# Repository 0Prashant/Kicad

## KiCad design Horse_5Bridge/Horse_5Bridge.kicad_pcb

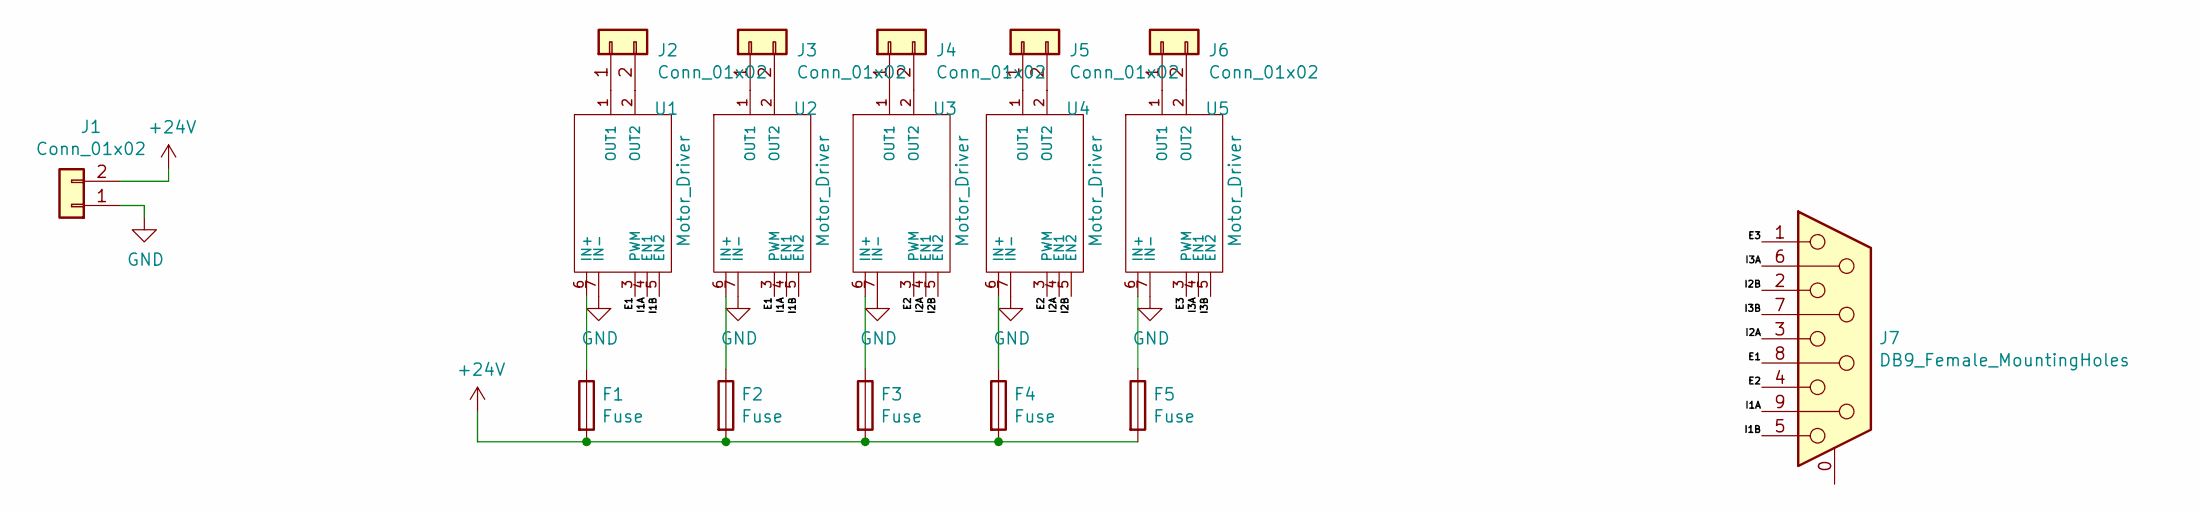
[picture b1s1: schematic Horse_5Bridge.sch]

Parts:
F1, F2, F3, F4, F5: Fuse; Fuse_Holder
J1, J2, J3, J4, J5, J6: Conn_01x02; Solar_Connector
J7: DB9_Female_MountingHoles; Connector_DB_9
U1, U2, U3, U4, U5: Motor_Driver; H_Bridge

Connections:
+24V: F1.2, F2.2, F3.2, F4.2, F5.2, J1.2
/E1: J7.8, U1.3 (PWM), U2.3 (PWM)
/E2: J7.4, U3.3 (PWM), U4.3 (PWM)
/E3: J7.1, U5.3 (PWM)
/I1A: J7.9, U1.4 (EN1), U2.4 (EN1)
/I1B: J7.5, U1.5 (EN2), U2.5 (EN2)
/I2A: J7.3, U3.4 (EN1), U4.4 (EN1)
/I2B: J7.2, U3.5 (EN2), U4.5 (EN2)
/I3A: J7.6, U5.4 (EN1)
/I3B: J7.7, U5.5 (EN2)
GND: J1.1, U1.7 (IN-), U2.7 (IN-), U3.7 (IN-), U4.7 (IN-), U5.7 (IN-)
unnamed: F1.1, U1.6 (IN+)
unnamed: F2.1, U2.6 (IN+)
unnamed: F3.1, U3.6 (IN+)
unnamed: F4.1, U4.6 (IN+)
unnamed: F5.1, U5.6 (IN+)
unnamed: J2.1, U1.1 (OUT1)
unnamed: J2.2, U1.2 (OUT2)
unnamed: J3.1, U2.1 (OUT1)
unnamed: J3.2, U2.2 (OUT2)
unnamed: J4.1, U3.1 (OUT1)
unnamed: J4.2, U3.2 (OUT2)
unnamed: J5.1, U4.1 (OUT1)
unnamed: J5.2, U4.2 (OUT2)
unnamed: J6.1, U5.1 (OUT1)
unnamed: J6.2, U5.2 (OUT2)

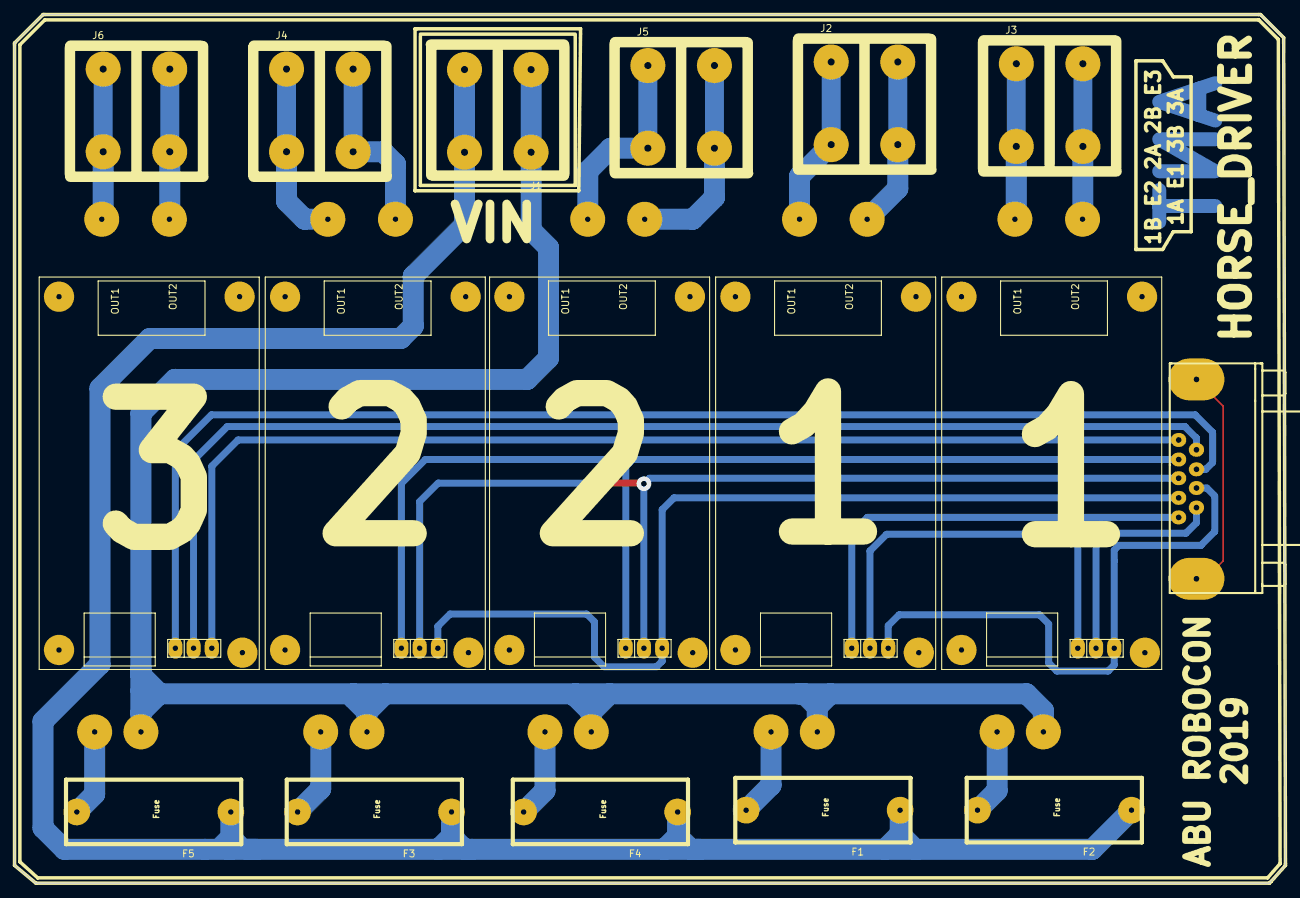
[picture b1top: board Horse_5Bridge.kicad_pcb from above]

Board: 2 copper layers, 181.4 x 124.0 mm, 17 parts (0 on the bottom side), 26 nets.

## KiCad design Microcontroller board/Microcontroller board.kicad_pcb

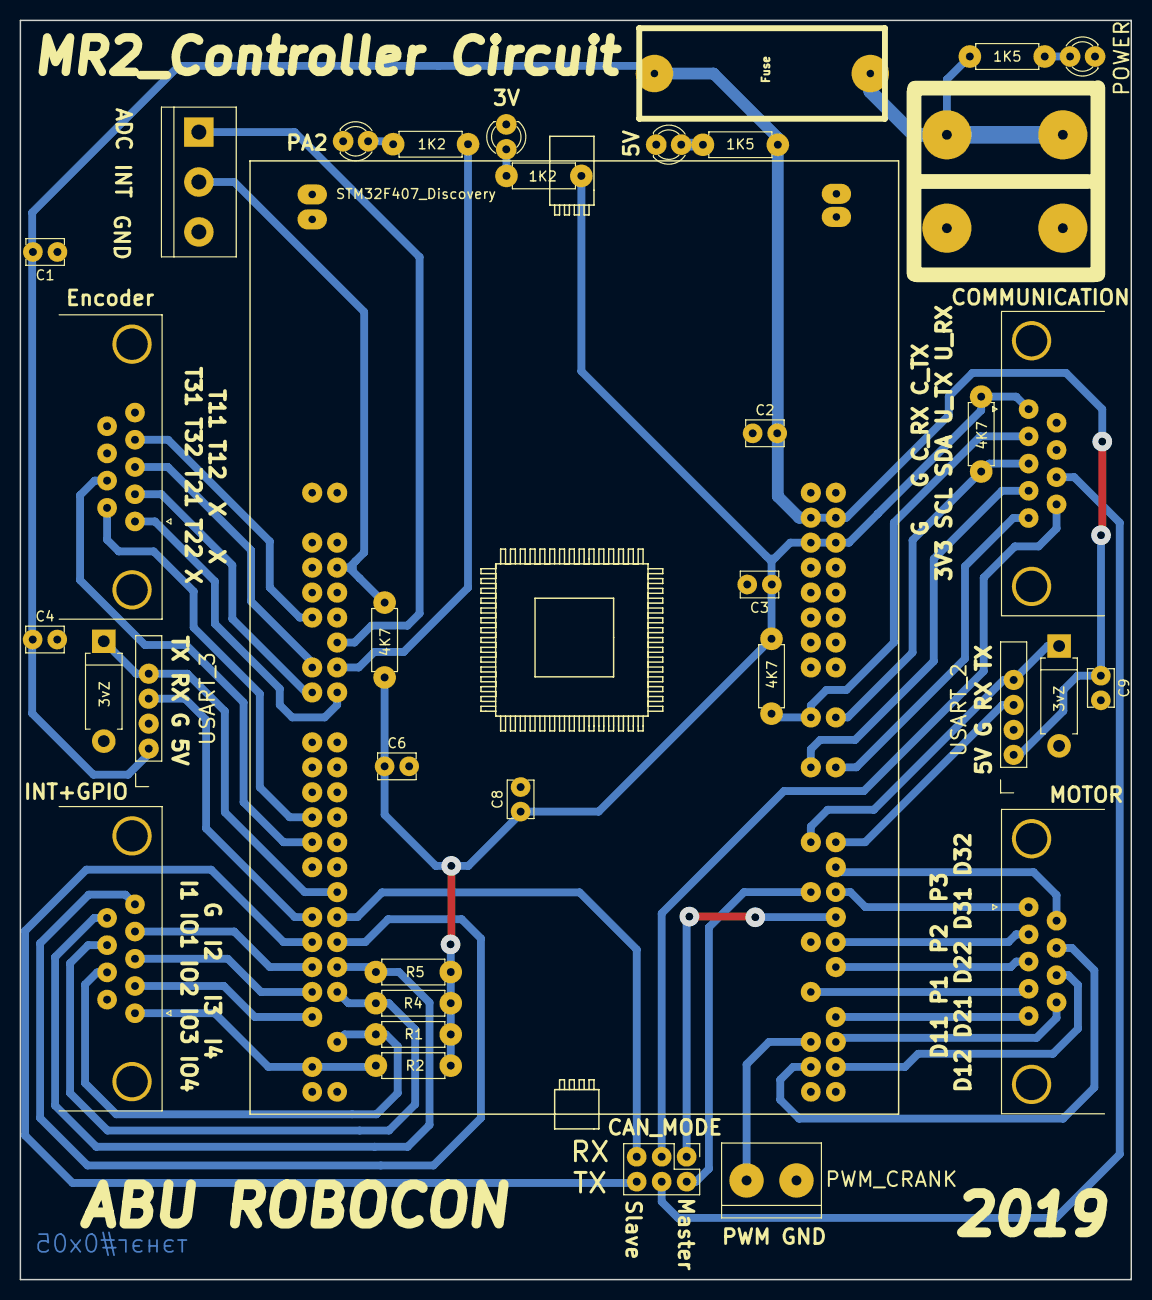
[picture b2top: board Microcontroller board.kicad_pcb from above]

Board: 2 copper layers, 113.0 x 128.1 mm, 36 parts (0 on the bottom side), 49 nets.

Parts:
3vZ, 3vZ#2: D_Zener; Diode_Small
4K7, 4K7#2: R; Resistor_small
C1, C2, C3, C4, C6, C8, C9: C; Capacitor_Disc_Small
D3, D4, D5, D6: LED; LED_D3.0mm
F1: Fuse; Fuse_Holder
J2: COMMUNICATION; DSUB-9_Female_Horizontal_P2.77x2.84mm_EdgePinOffset4.94mm_H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
J3: Encoder; DSUB-9_Female_Horizontal_P2.77x2.84mm_EdgePinOffset4.94mm_H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
J4: MOTOR; DSUB-9_Female_Horizontal_P2.77x2.84mm_EdgePinOffset4.94mm_H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
J5: USART_2; PinSocket_1x06_P2.54mm_Vertical
J6: INT+GPIO; DSUB-9_Female_Horizontal_P2.77x2.84mm_EdgePinOffset4.94mm_H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
J7: USART_3; PinSocket_1x06_P2.54mm_Vertical
J8: PWM_CRANK; Connector_Bornier_2
J9: INTERRUPT; TerminalBlock_bornier-3_P5.08mm
J11: POWER; Solar_Connector
R1, R2, R4, R5: R; Resistor_small
R7: 4K7; Resistor_small
R8, R9: 1K5; Resistor_small
R10, R11: 1K2; Resistor_small
U1: STM32F407_Discovery
`J10: CAN_MODE; PinHeader_2x03_P2.54mm_Vertical

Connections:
/3V3: 4K7.1, 4K7#2.2, C3.1, C6.1, C8.1, J2.1, R1.1, R2.1, R4.2, R5.2, R7.1, R11.2, U1.55, U1.56
/5V: C1.2, C2.2, C4.1, C9.1, F1.1, J5.2, J7.2, R9.2, U1.53, U1.54
/CAN_RX: J2.9, `J10.2
/CAN_TX: J2.8, `J10.5
/GND: 3vZ.2, 3vZ#2.2, C1.1, C2.1, C3.2, C4.2, C6.2, C8.2, C9.2, D3.1, D4.1, D5.1, D6.1, J2.0, J2.6, J2.7, J3.0, J4.0, J5.3, J6.0, J6.6, J7.3, J8.2, J9.3, J11.1, U1.1, U1.2, U1.5, U1.23, U1.49, U1.50, U1.51, U1.52, U1.99, U1.100
/PA1: J3.4, U1.11
/PA2: J9.1, U1.14
/PA4: R10.2, U1.16
/PA5: J3.3, U1.15
/PA6: J3.1, U1.18
/PA7: J3.2, U1.17
/PA9: J4.5, U1.94
/PA10: J4.4, U1.91
/PA15: J4.3, U1.90
/PB6: J2.4, U1.73
/PB7: J2.5, U1.74
/PB8: 4K7#2.1, J2.2, U1.69
/PB9: 4K7.2, J2.3, U1.70
/PB10: 3vZ#2.1, J7.5, U1.34
/PB11: J7.4, U1.35
/PB12: U1.36, `J10.3
/PB13: U1.37, `J10.6
/PB14: J6.5, U1.38
/PB15: J6.4, U1.39
/PC0: J9.2, R7.2, U1.8
/PC6: J4.7, U1.97
/PC7: J4.8, U1.98
/PC8: J8.1, U1.95
/PC9: J4.9, U1.96
/PC11: J4.2, U1.88
/PD0: U1.86, `J10.1
/PD1: U1.83, `J10.4
/PD2: J4.1, U1.84
/PD4: J4.6, U1.82
/PD5: 3vZ.1, J5.5, U1.79
/PD6: J5.4, U1.80
/PD8: J6.9, R5.1, U1.40
/PD9: J6.3, U1.41
/PD10: J6.8, R4.1, U1.42
/PD11: J6.2, U1.43
/PD14: J6.7, R1.2, U1.46
/PD15: J6.1, R2.2, U1.47
/PE9: J3.6, U1.27
/PE11: J3.7, U1.29
/Vin: F1.2, J11.2, R8.2
unnamed: D3.2, R8.1
unnamed: D4.2, R9.1
unnamed: D5.2, R10.1
unnamed: D6.2, R11.1

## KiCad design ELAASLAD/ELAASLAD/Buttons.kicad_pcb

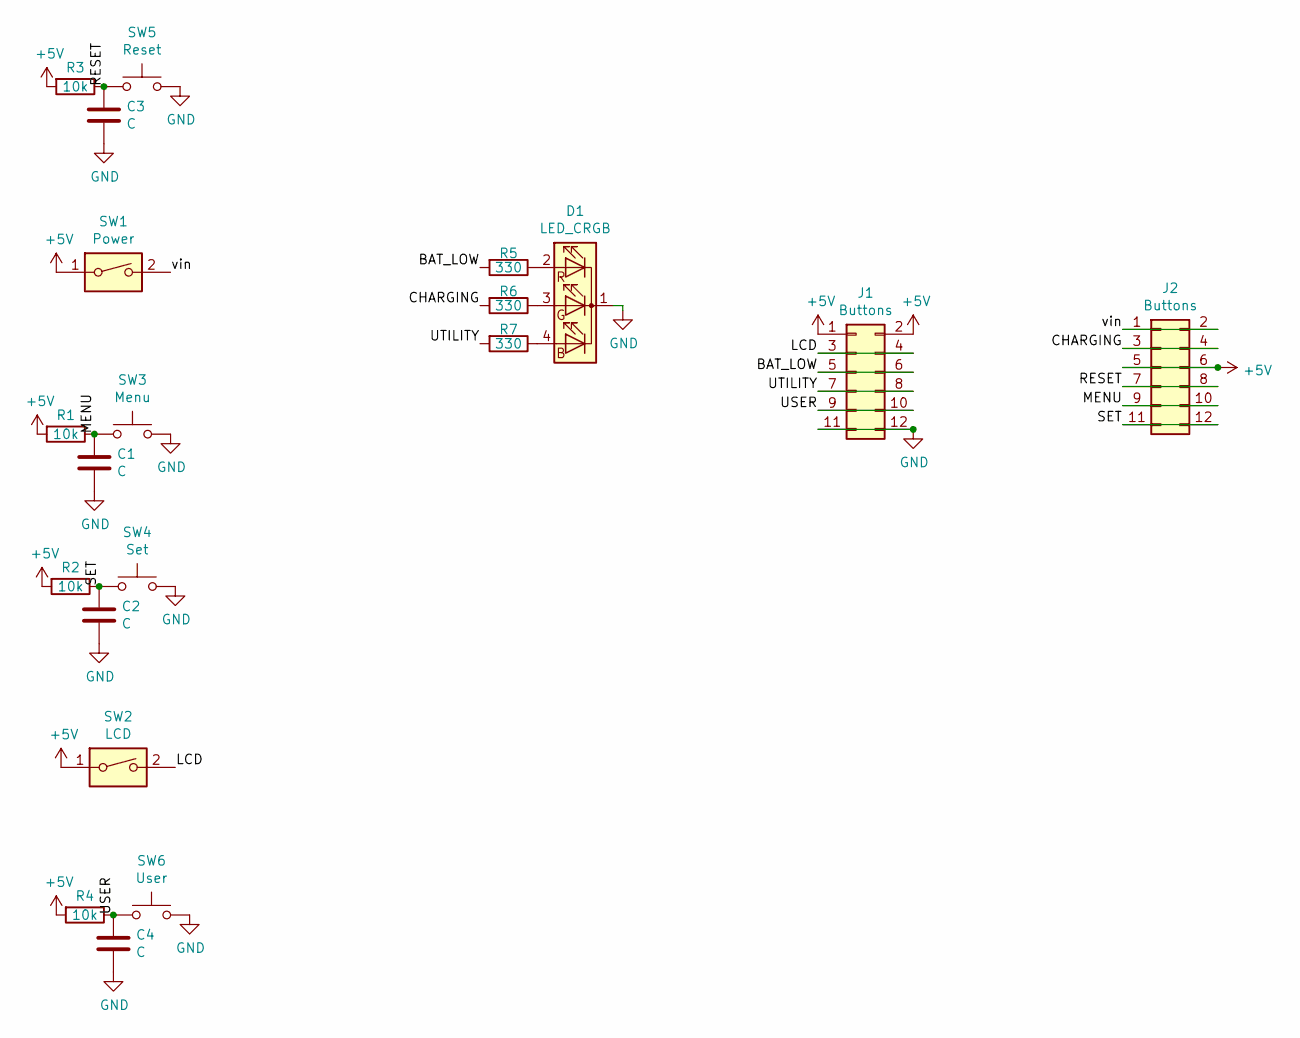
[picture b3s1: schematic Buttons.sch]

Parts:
C1, C2, C3, C4: C; Capacitor_Disc_Small
D1: LED_CRGB; LED_D5.0mm-4
J1, J2: Buttons; Pin_Header_Straight_2x06_Pitch2.54mm
R1, R2, R3, R4: 10k; Resistor_small
R5, R6, R7: 330; Resistor_small
SW1: Power; DIP_Switch
SW2: LCD; DIP_Switch
SW3: Menu; SW_PUSH-12mm
SW4: Set; SW_PUSH-12mm
SW5: Reset; SW_PUSH-12mm
SW6: User; SW_PUSH-12mm

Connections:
+5V: J1.1, J1.2, J2.5, J2.6, R1.2, R2.2, R3.2, R4.2, SW1.1, SW2.1
/BAT_LOW: J1.5, J1.6, R5.2
/CHARGING: J2.3, J2.4, R6.2
/LCD: J1.3, J1.4, SW2.2
/MENU: C1.1, J2.9, J2.10, R1.1, SW3.1
/RESET: C3.1, J2.7, J2.8, R3.1, SW5.1
/SET: C2.1, J2.11, J2.12, R2.1, SW4.1
/USER: C4.1, J1.9, J1.10, R4.1, SW6.1
/UTILITY: J1.7, J1.8, R7.2
/vin: J2.1, J2.2, SW1.2
GND: C1.2, C2.2, C3.2, C4.2, D1.1 (K), J1.11, J1.12, SW3.2, SW4.2, SW5.2, SW6.2
unnamed: D1.2 (RA), R5.1
unnamed: D1.3 (GA), R6.1
unnamed: D1.4 (BA), R7.1

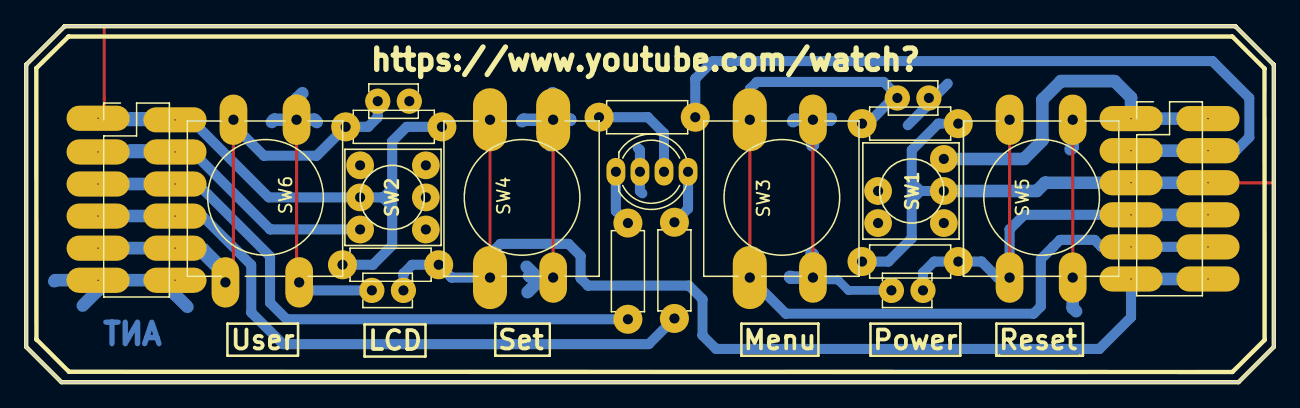
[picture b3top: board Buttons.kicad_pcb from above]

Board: 2 copper layers, 98.8 x 28.2 mm, 20 parts (0 on the bottom side), 14 nets.

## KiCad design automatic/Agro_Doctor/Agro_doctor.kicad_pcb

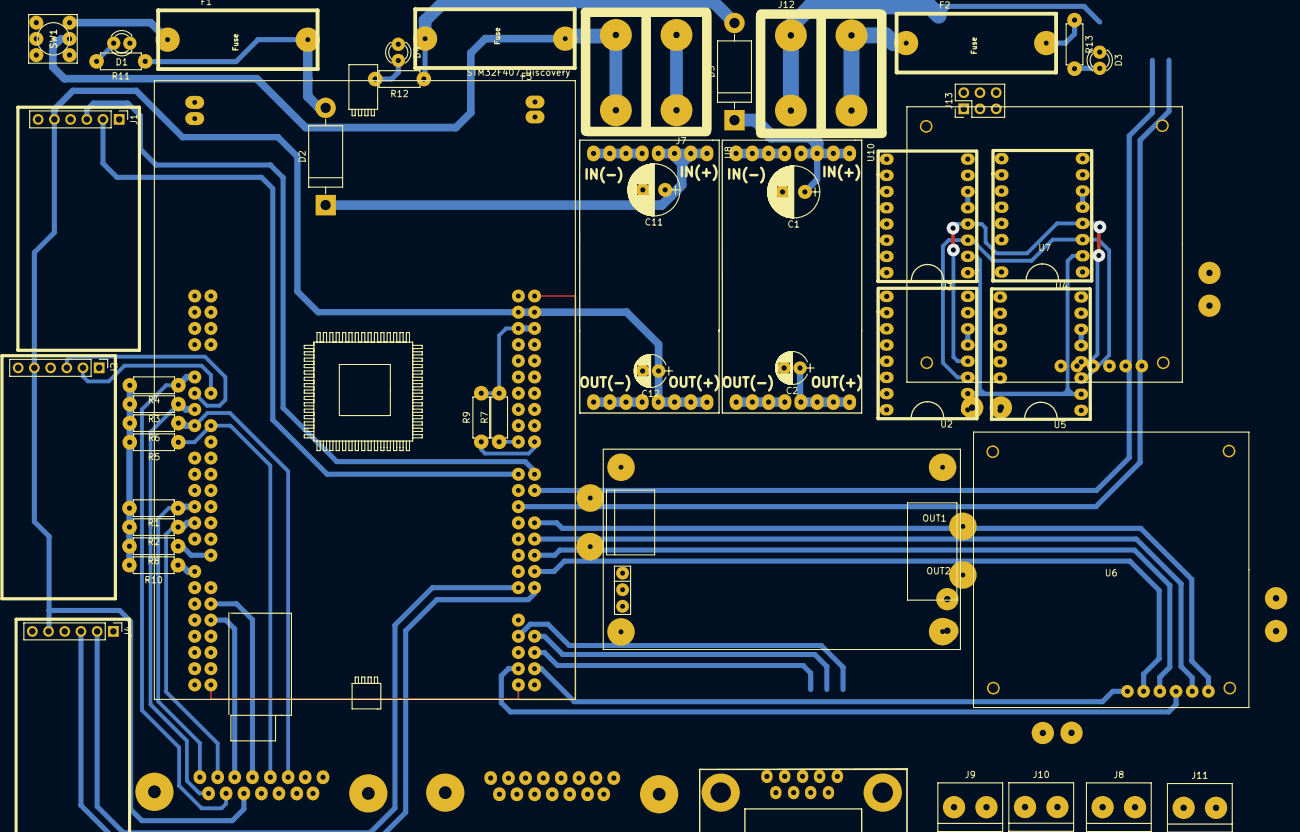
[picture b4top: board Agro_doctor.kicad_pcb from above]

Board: 2 copper layers, 49 parts (0 on the bottom side), 78 nets.

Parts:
C1, C11: 100uf; Capacitor_100uF
C2, C12: 10uf; Capacitor_10uF
D1, D3, D4: LED; LED_D3.0mm
D2, D5: D; Diode_Medium
F1, F2, F3: Fuse; Fuse_Holder
J1, J2, J4: Bluetooth; Pin_Header_Straight_1x06_Pitch2.54mm
J3: 3STEPPER,1SERVO; Connector_DB15
J5: Encoders, Stepper1; Connector_DB15
J6: 3 MPU, HUMIDITY, PH; Connector_DB_9
J7: Power_Logic; Solar_Connector
J8: M1; Connector_Bornier_2
J9: M4; Connector_Bornier_2
J10: M2; Connector_Bornier_2
J11: M3; Connector_Bornier_2
J12: Power_Motor; Solar_Connector
J13: MS_Conn; Pin_Header_Straight_2x03_Pitch2.54mm
R1, R2, R3, R4, R5, R6, R7, R8, R9, R10: 10K; Resistor_small
R11, R13: 1k5; Resistor_small
R12: R; Resistor_small
SW1: SW_DIP_x01; DIP_Switch
U1: Motor_Driver; H_Bridge
U2: A4988_1; A4998
U3: A4988_2; A4998
U4: A4988_3; A4998
U5: A4988_4; A4998
U6: L298_M2,3; L298
U7: L298_M4; L298
U8: Buck; Buck_Regulator
U9: STM32F407_Discovery
U10: Boost; Buck_Regulator

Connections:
+3V3: J6.5, R1.2, R2.2, R3.2, R4.2, R5.2, R6.2, R7.2, R8.2, R9.2, R10.2, U9.55, U9.56
+5V: C12.1, J1.5, J2.5, J3.8, J4.5, J5.13, J6.9, J13.4, J13.5, J13.6, U2.10, U3.10, U4.10, U5.10, U8.3, U9.53, U9.54
+12V: F3.2, J7.2, SW1.1
/12VMOT: F2.1, R13.1, U1.6, U6.1, U7.1
/18V: C2.1, U2.16, U3.16, U4.16, U5.16, U10.3
/E1_CHA: J5.8, R1.1, U9.27
/E1_CHB: J5.7, R2.1, U9.29
/E2_CHA: J5.15, R3.1, U9.15
/E2_CHB: J5.14, R4.1, U9.11
/E3_CHA: J5.4, R5.1, U9.18
/E3_CHB: J5.3, R6.1, U9.17
/GMOT: D3.1, J12.1, U1.7, U6.2, U7.2
/I2C1_SCL: J6.7, R7.1, U9.69
/I2C1_SDA: J6.6, R9.1, U9.70
/I2C2_SCL: J6.4, R8.1, U9.34
/I2C2_SDA: J6.1, R10.1, U9.35
/INT1: J5.5, U9.40
/INT2: J5.6, U9.42
/M1_EN1: U1.4, U9.76
/M1_EN2: U1.5, U9.77
/M1_PWM: U1.3, U9.95
/M2_EN1: U6.4, U9.86
/M2_EN2: U6.5, U9.84
/M2_PWM: U6.3, U9.98
/M3_EN1: U6.7, U9.82
/M3_EN2: U6.8, U9.80
/M3_PWM: U6.6, U9.97
/M4_EN1: U7.7, U9.94
/M4_EN2: U7.8, U9.93
/M4_PWM: U7.6, U9.96
/MS1: J13.1, U2.2, U3.2, U4.2, U5.2
/MS2: J13.2, U2.3, U3.3, U4.3, U5.3
/MS3: J13.3, U2.4, U3.4, U4.4, U5.4
/S1_1A: J5.9, U2.12
/S1_1B: J5.1, U2.11
/S1_2A: J5.2, U2.13
/S1_2B: J5.10, U2.14
/S2_1A: J3.2, U3.12
/S2_1B: J3.10, U3.11
/S2_2A: J3.9, U3.13
/S2_2B: J3.1, U3.14
/S3_1A: J3.4, U4.12
/S3_1B: J3.12, U4.11
/S3_2A: J3.11, U4.13
/S3_2B: J3.3, U4.14
/S4_1A: J3.6, U5.12
/S4_1B: J3.14, U5.11
/S4_2A: J3.13, U5.13
/S4_2B: J3.5, U5.14
/SERVO: J3.15, U9.91
/U1_RX: J1.3, U9.74
/U1_TX: J1.2, U9.73
/U2_RX: J2.3, U9.13
/U2_TX: J2.2, U9.14
/U3_RX: J4.3, U9.88
/U3_TX: J4.2, U9.87
GND: C1.2, C2.2, C11.2, C12.2, D1.1, D4.1, J1.4, J2.4, J3.7, J4.4, J5.11, J5.12, J6.8, J7.1, U2.9, U3.9, U4.9, U5.9, U8.2, U8.4, U9.1, U9.2, U9.49, U9.50, U9.51, U9.52, U9.99, U9.100, U10.2, U10.4
unnamed: C1.1, D5.1, U10.1
unnamed: C11.1, D2.1, U8.1
unnamed: D1.2, R11.2
unnamed: D2.2, F1.1, R11.1
unnamed: D3.2, R13.2
unnamed: D4.2, R12.2
unnamed: D5.2, F3.1, R12.1
unnamed: F1.2, SW1.2
unnamed: F2.2, J12.2
unnamed: J8.1, U1.1
unnamed: J8.2, U1.2
unnamed: J9.1, U7.11
unnamed: J9.2, U7.12
unnamed: J10.1, U6.10
unnamed: J10.2, U6.9
unnamed: J11.1, U6.11
unnamed: J11.2, U6.12
unnamed: U2.5, U2.6
unnamed: U3.5, U3.6
unnamed: U4.5, U4.6
unnamed: U5.5, U5.6

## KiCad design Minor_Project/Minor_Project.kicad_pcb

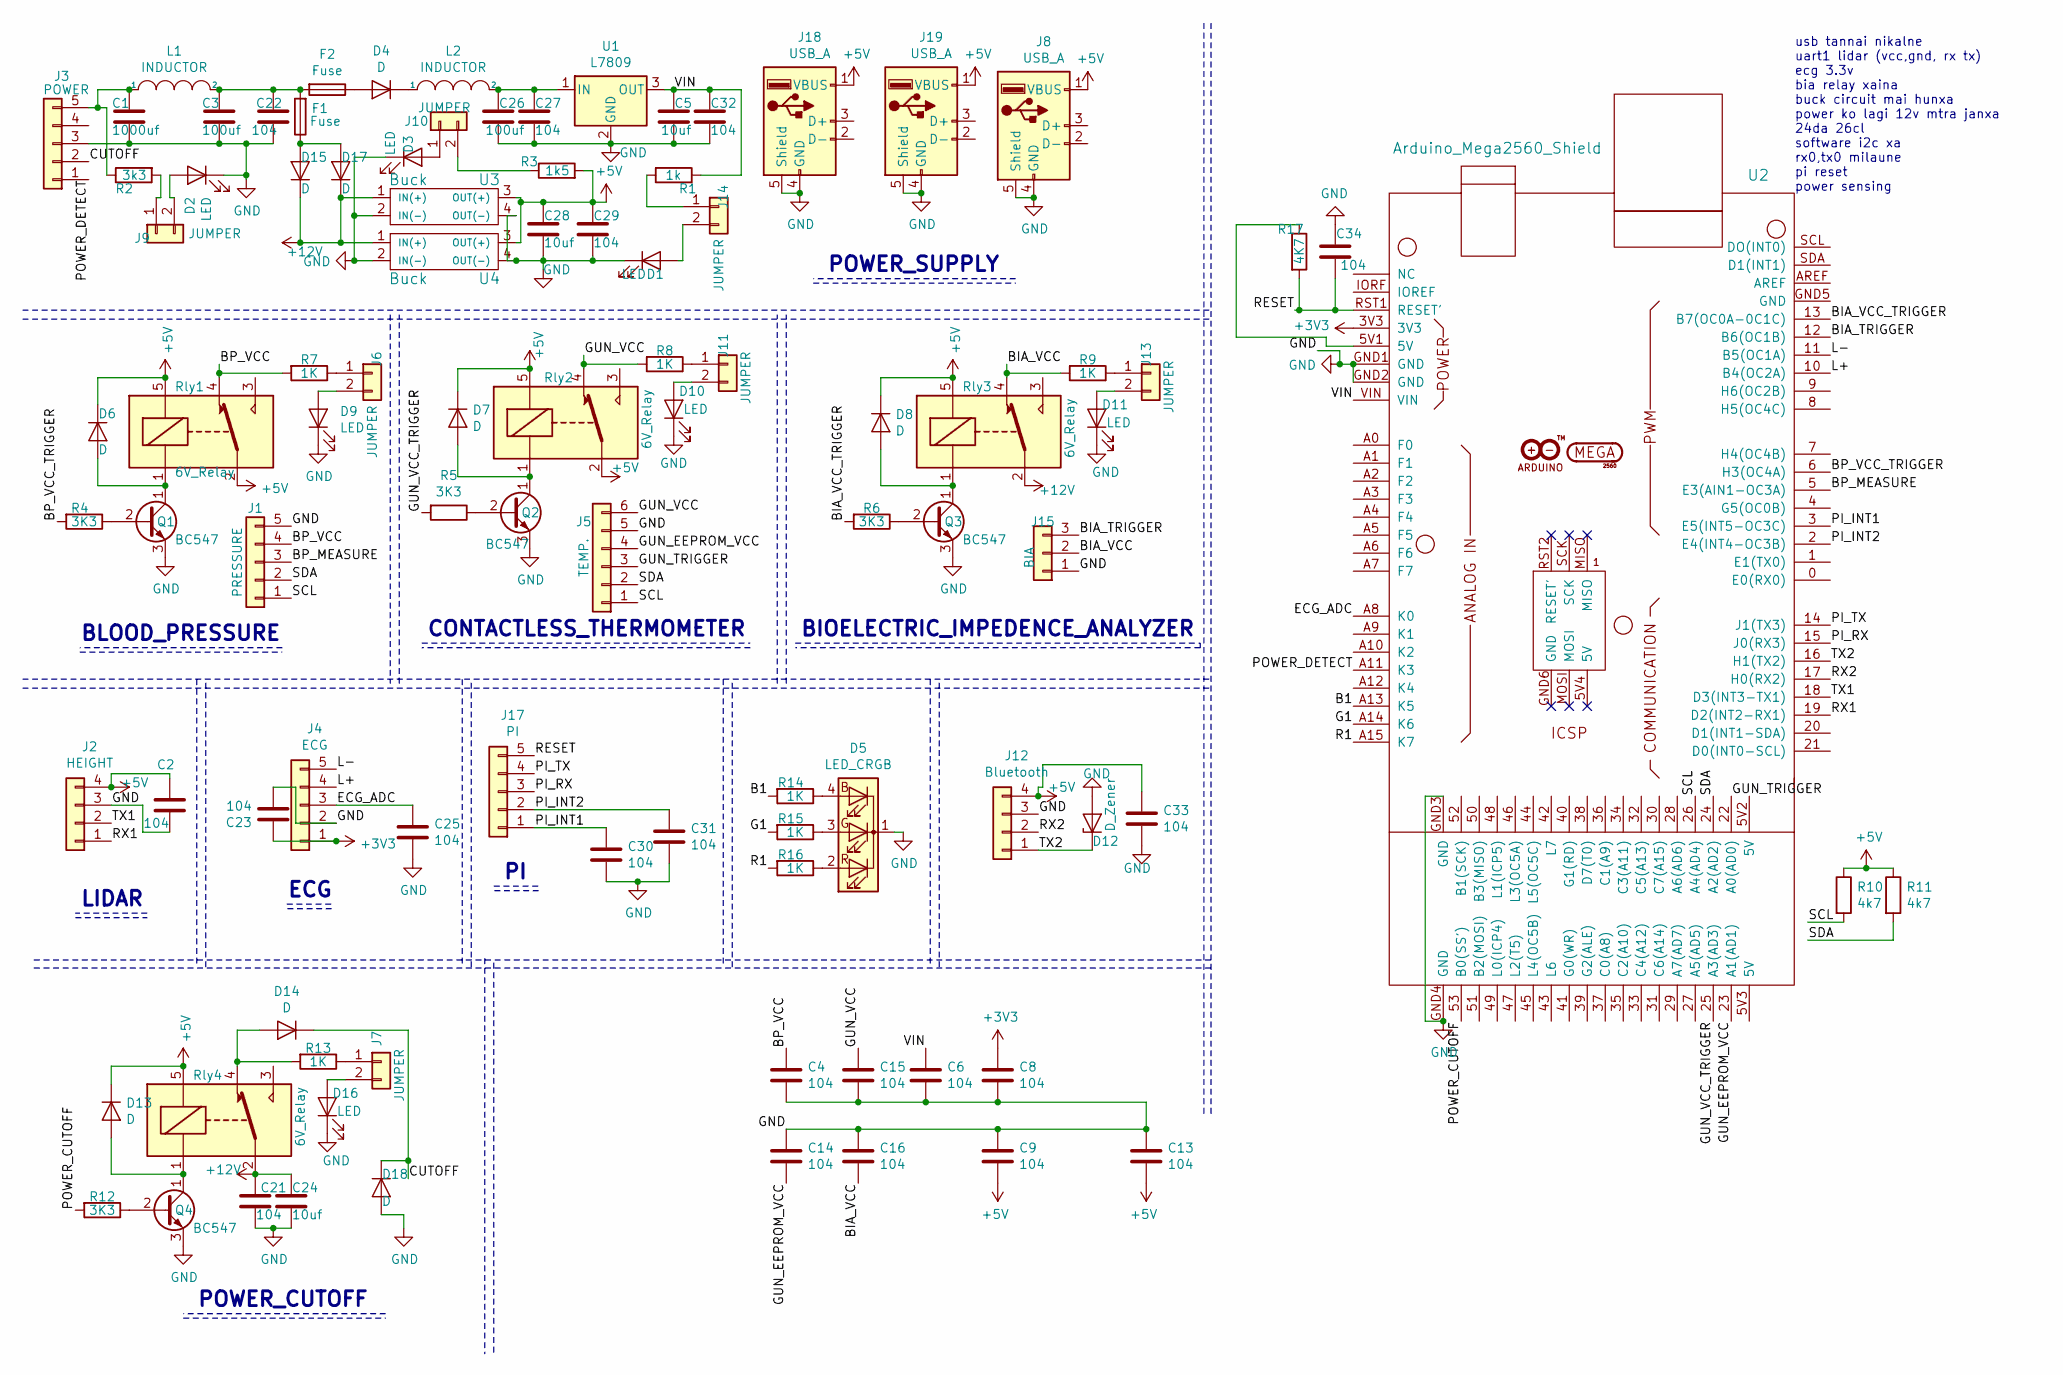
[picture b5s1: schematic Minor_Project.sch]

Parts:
C1: 1000uf; Capacitor_1000uF
C2, C4, C6, C8, C9, C13, C14, C15, C16, C21, C22, C23, C25, C27, C29, C30, C31, C32, C33, C34: 104; Capacitor_Disc_Small
C3, C26: 100uf; Capacitor_100uF
C5, C24, C28: 10uf; Capacitor_10uF
D1, D2, D3, D9, D10, D11, D16: LED; LED_D3.0mm
D4, D6, D7, D8, D13, D14, D18: D; Diode_Small
D5: LED_CRGB; LED_D5.0mm-4
D12: D_Zener; D_A-405_P7.62mm_Horizontal
D15, D17: D; Diode_Medium
F1, F2: Fuse; Fuse_Holder
J1: PRESSURE; JST_XH_B05B-XH-A_05x2.50mm_Straight
J2: HEIGHT; JST_XH_B04B-XH-A_04x2.50mm_Straight
J3: POWER; JST_XH_B05B-XH-A_05x2.50mm_Straight
J4: ECG; JST_XH_B05B-XH-A_05x2.50mm_Straight
J5: TEMP.; JST_XH_B06B-XH-A_06x2.50mm_Straight
J6, J7, J9, J10, J11, J13, J14: JUMPER; Pin_Header_Straight_1x02_Pitch2.54mm
J8, J18, J19: USB_A; Connector_USB
J12: Bluetooth; Socket_Strip_Straight_1x04_Pitch2.54mm
J15: BIA; JST_XH_B03B-XH-A_03x2.50mm_Straight
J17: PI; JST_XH_B05B-XH-A_05x2.50mm_Straight
L1, L2: INDUCTOR; L_Radial_D9.5mm_P5.00mm_Fastron_07HVP
Q1, Q2, Q3, Q4: BC547
R1: 1k; Resistor_small
R2: 3k3; Resistor_small
R3: 1k5; Resistor_small
R4, R5, R6, R12: 3K3; Resistor_small
R7, R8, R9, R13, R14, R15, R16: 1K; Resistor_small
R10, R11: 4k7; Resistor_small
R17: 4K7; Resistor_small
Rly1, Rly2, Rly3, Rly4: 6V_Relay; Relay_6V
U1: L7809; TO-220_Horizontal
U2: Arduino_Mega2560_Shield
U3, U4: Buck; Buck_Regulator

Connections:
+3V3: C8.1, C23.1, J4.1, U2.3V3
+5V: C2.1, C9.2, C13.2, C28.1, C29.1, C33.1, D6.1 (K), D7.1 (K), D8.1 (K), D13.1 (K), J2.4, J8.1 (VBUS), J12.4, J18.1 (VBUS), J19.1 (VBUS), R3.2, R10.1, R11.1, Rly1.2, Rly1.5, Rly2.2, Rly2.5, Rly3.5, Rly4.5, U3.3 (OUT(+)), U4.3 (OUT(+))
+12V: C21.1, C24.1, D15.1 (K), D17.1 (K), Rly3.2, Rly4.2, U3.1 (IN(+)), U4.1 (IN(+))
/B1: R14.2, U2.A13 (K5)
/BIA_TRIGGER: J15.3, U2.12 (B6(OC1B))
/BIA_VCC: C16.2, J15.2, R9.2, Rly3.4
/BIA_VCC_TRIGGER: R6.2, U2.13 (B7(OC0A-0C1C))
/BP_MEASURE: J1.3, U2.5 (E3(AIN1-OC3A))
/BP_VCC: C4.1, J1.4, R7.2, Rly1.4
/BP_VCC_TRIGGER: R4.2, U2.6 (H3(OC4A))
/CUTOFF: D14.1 (K), D18.1 (K), J3.2
/ECG_ADC: C25.1, J4.3, U2.A8 (K0)
/G1: R15.2, U2.A14 (K6)
/GUN_EEPROM_VCC: C14.2, J5.4, U2.23 (A1(AD1))
/GUN_TRIGGER: J5.3, U2.22 (A0(AD0))
/GUN_VCC: C15.1, J5.6, R8.2, Rly2.4
/GUN_VCC_TRIGGER: R5.2, U2.25 (A3(AD3))
/L+: J4.4, U2.10 (B4(OC2A))
/L-: J4.5, U2.11 (B5(OC1A))
/PI_INT1: C30.1, J17.1, U2.3 (E5(INT5-OC3C))
/PI_INT2: C31.1, J17.2, U2.2 (E4(INT4-OC3B))
/PI_RX: J17.3, U2.15 (J0(RX3))
/PI_TX: J17.4, U2.14 (J1(TX3))
/POWER_CUTOFF: R12.2, U2.53 (B0(SS'))
/POWER_DETECT: J3.1, U2.A11 (K3)
/R1: R16.2, U2.A15 (K7)
/RESET: C34.2, J17.5, R17.2, U2.RST1 (RESET')
/RX1: J2.1, U2.19 (D2(INT2-RX1))
/RX2: J12.2, U2.17 (H0(RX2))
/SCL: J1.1, J5.1, R10.2, U2.26 (A4(AD4))
/SDA: J1.2, J5.2, R11.2, U2.24 (A2(AD2))
/TX1: J2.2, U2.18 (D3(INT3-TX1))
/TX2: D12.1 (K), J12.1, U2.16 (H1(TX2))
/VIN: C5.1, C6.1, C32.1, R1.1, U1.3 (OUT), U2.VIN
GND: C1.2, C2.2, C3.2, C4.2, C5.2, C6.2, C8.2, C9.1, C13.1, C14.1, C15.2, C16.1, C21.2, C22.2, C23.2, C24.2, C25.2, C26.2, C27.2, C28.2, C29.2, C30.2, C31.2, C32.2, C33.2, C34.1, D1.1 (K), D2.1 (K), D3.1 (K), D5.1 (K), D9.1 (K), D10.1 (K), D11.1 (K), D12.2 (A), D16.1 (K), D18.2 (A), J1.5, J2.3, J3.3, J4.2, J5.5, J8.4 (GND), J8.5 (Shield), J12.3, J15.1, J18.4 (GND), J18.5 (Shield), J19.4 (GND), J19.5 (Shield), Q1.3 (E), Q2.3 (E), Q3.3 (E), Q4.3 (E), U1.2 (GND), U2.GND1 (GND), U2.GND2 (GND), U2.GND3 (GND), U2.GND4 (GND), U3.2 (IN(-)), U3.4 (OUT(-)), U4.2 (IN(-)), U4.4 (OUT(-))
unnamed: C1.1, J3.5, L1.1, R2.1
unnamed: C3.1, C22.1, F1.2, F2.2, L1.2
unnamed: C26.1, C27.1, L2.2, U1.1 (IN)
unnamed: D1.2 (A), J14.2
unnamed: D2.2 (A), J9.2
unnamed: D3.2 (A), J10.1
unnamed: D4.1 (K), L2.1
unnamed: D4.2 (A), F2.1
unnamed: D5.2 (RA), R16.1
unnamed: D5.3 (GA), R15.1
unnamed: D5.4 (BA), R14.1
unnamed: D6.2 (A), Q1.1 (C), Rly1.1
unnamed: D7.2 (A), Q2.1 (C), Rly2.1
unnamed: D8.2 (A), Q3.1 (C), Rly3.1
unnamed: D9.2 (A), J6.2
unnamed: D10.2 (A), J11.2
unnamed: D11.2 (A), J13.2
unnamed: D13.2 (A), Q4.1 (C), Rly4.1
unnamed: D14.2 (A), R13.2, Rly4.4
unnamed: D15.2 (A), D17.2 (A), F1.1
unnamed: D16.2 (A), J7.2
unnamed: J6.1, R7.1
unnamed: J7.1, R13.1
unnamed: J9.1, R2.2
unnamed: J10.2, R3.1
unnamed: J11.1, R8.1
unnamed: J13.1, R9.1
unnamed: J14.1, R1.2
unnamed: Q1.2 (B), R4.1
unnamed: Q2.2 (B), R5.1
unnamed: Q3.2 (B), R6.1
unnamed: Q4.2 (B), R12.1
unnamed: R17.1, U2.5V1 (5V)

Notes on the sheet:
CONTACTLESS_THERMOMETER
BLOOD_PRESSURE
BIOELECTRIC_IMPEDENCE_ANALYZER
LIDAR
ECG
usb tannai nikalne uart1 lidar (vcc,gnd, rx tx) ecg 3.3v bia relay xaina buck circuit mai hunxa power ko lagi 12v mtra janxa 24da 26cl software i2c xa rx0,tx0 milaune pi reset power sensing
POWER_SUPPLY
POWER_CUTOFF

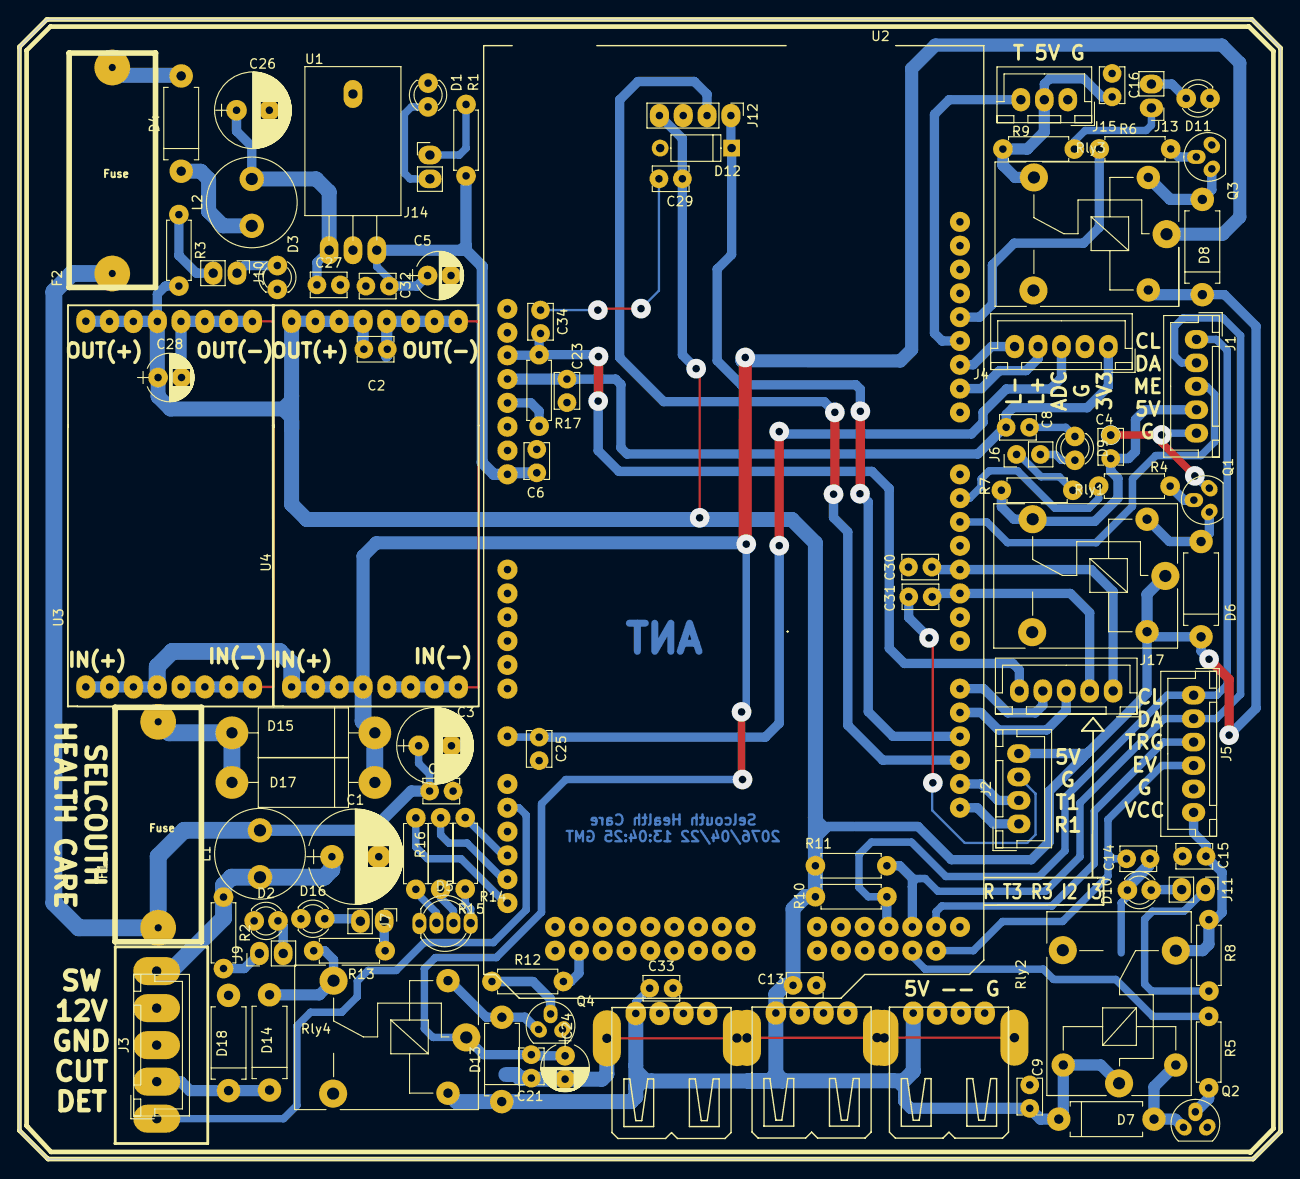
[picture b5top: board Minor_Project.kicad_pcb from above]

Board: 2 copper layers, 134.5 x 121.5 mm, 95 parts (0 on the bottom side), 68 nets.

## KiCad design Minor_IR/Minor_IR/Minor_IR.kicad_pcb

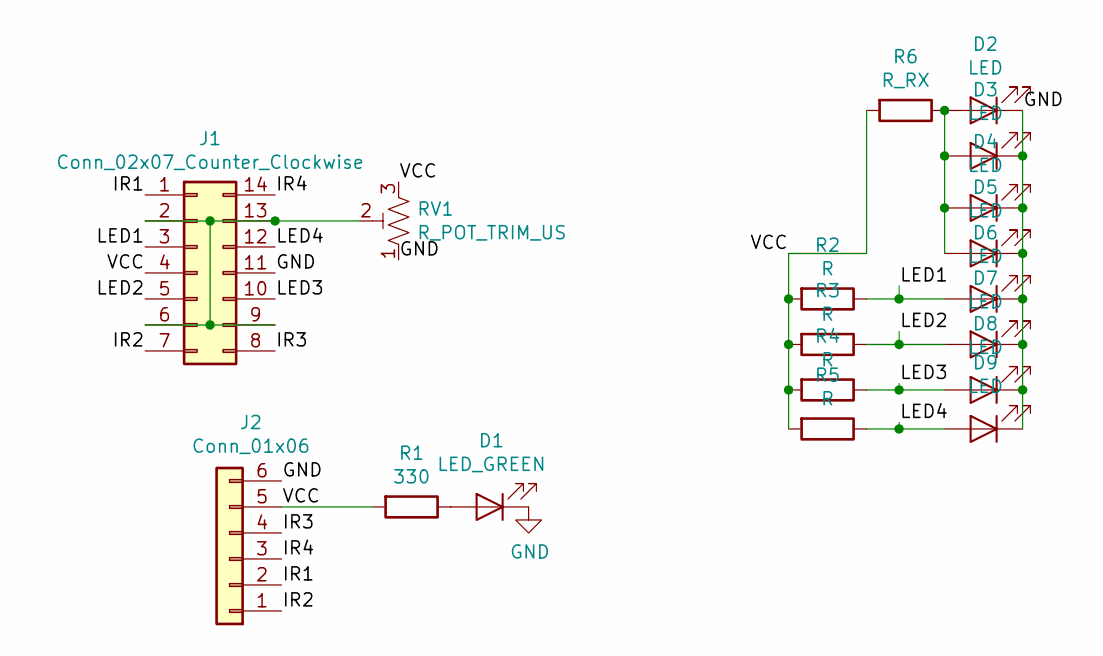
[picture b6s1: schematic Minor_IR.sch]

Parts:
D1: LED_GREEN; LED_D3.0mm
D2, D3, D4, D5, D6, D7, D8, D9: LED; LED_D3.0mm
J1: Conn_02x07_Counter_Clockwise; DIP-14_W7.62mm
J2: Conn_01x06; JST_XH_B06B-XH-A_06x2.50mm_Straight
R1: 330; Resistor_small
R2, R3, R4, R5: R; Resistor_small
R6: R_RX; Resistor_small
RV1: R_POT_TRIM_US; Potentiometer_Triwood

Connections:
/IR1: J1.1, J2.2
/IR2: J1.7, J2.1
/IR3: J1.8, J2.4
/IR4: J1.14, J2.3
/LED1: D6.2 (A), J1.3, R2.1
/LED2: D7.2 (A), J1.5, R3.1
/LED3: D8.2 (A), J1.10, R4.1
/LED4: D9.2 (A), J1.12, R5.1
/VCC: J1.4, J2.5, R1.2, R2.2, R3.2, R4.2, R5.2, R6.2, RV1.3
GND: D1.1 (K), D2.1 (K), D3.1 (K), D4.1 (K), D5.1 (K), D6.1 (K), D7.1 (K), D8.1 (K), D9.1 (K), J1.11, J2.6, RV1.1
unnamed: D1.2 (A), R1.1
unnamed: D2.2 (A), D3.2 (A), D4.2 (A), D5.2 (A), R6.1
unnamed: J1.2, J1.6, J1.9, J1.13, RV1.2

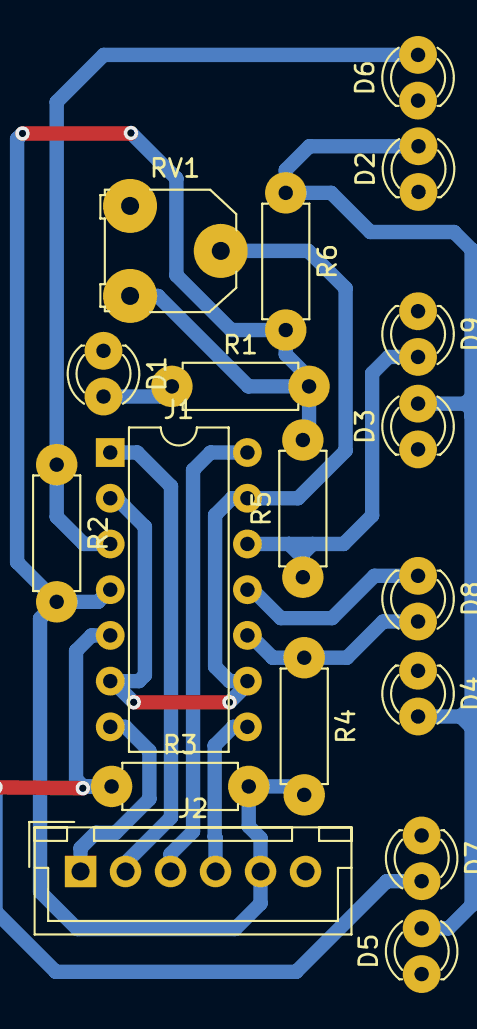
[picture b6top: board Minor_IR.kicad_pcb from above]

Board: 2 copper layers, 18 parts (0 on the bottom side), 13 nets.

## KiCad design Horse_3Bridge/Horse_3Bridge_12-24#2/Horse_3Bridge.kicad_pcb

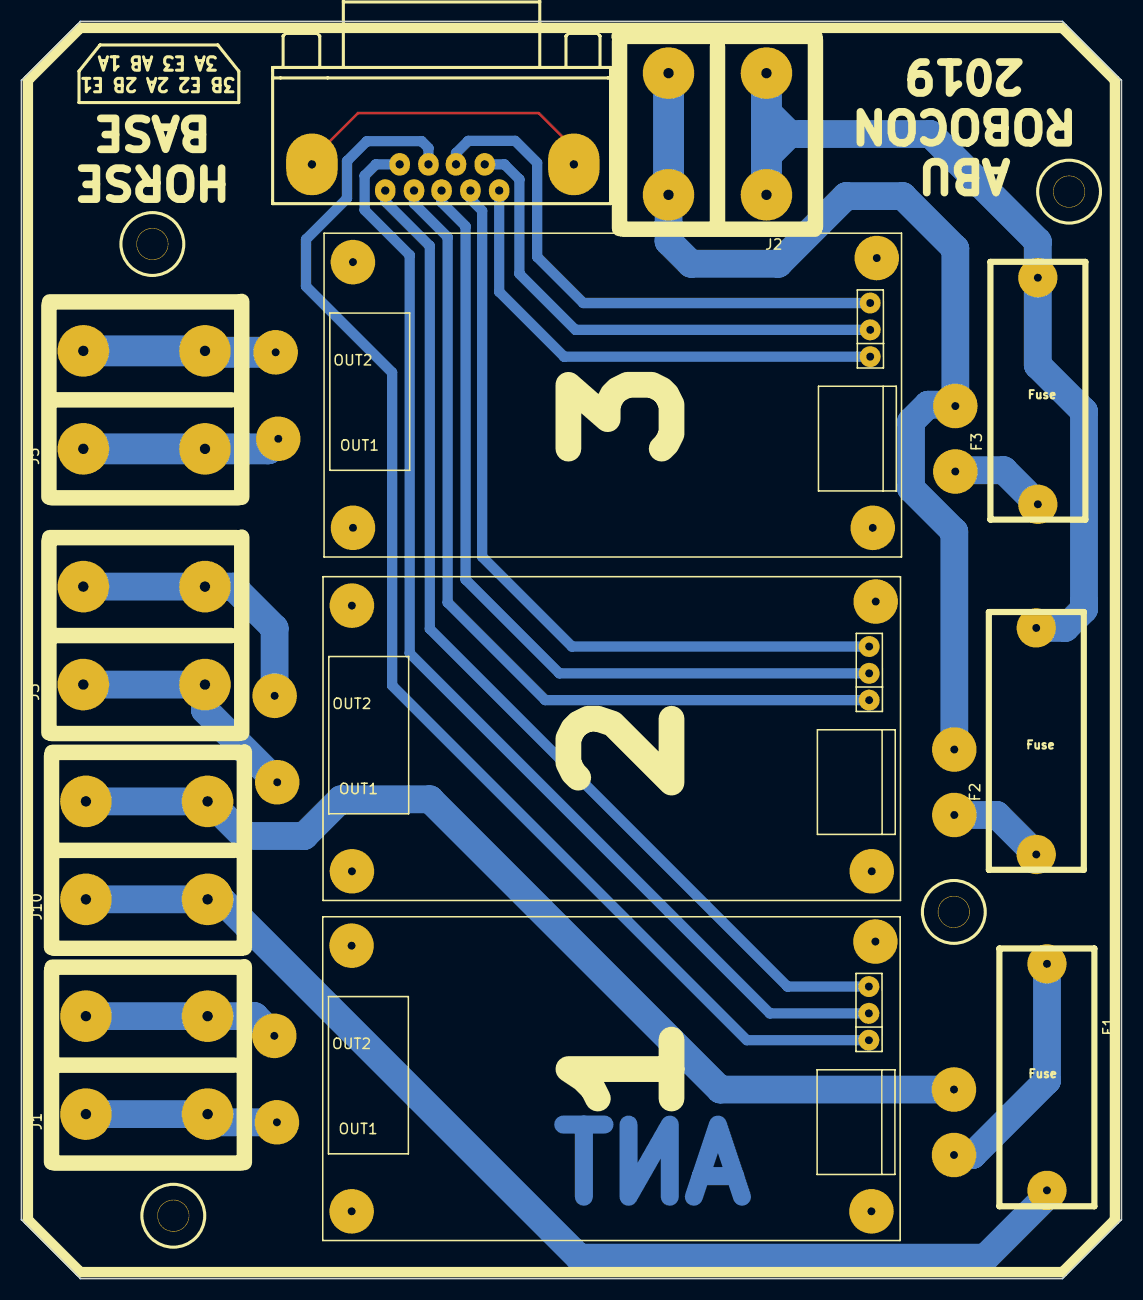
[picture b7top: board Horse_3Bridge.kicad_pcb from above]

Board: 2 copper layers, 106.7 x 121.9 mm, 16 parts (0 on the bottom side), 22 nets.

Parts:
F1, F2, F3: Fuse; Fuse_Holder
J1: M1; Solar_Connector
J2, J10: Power; Solar_Connector
J3: M2; Solar_Connector
J4: DB9_Female_MountingHoles; Connector_DB_9
J5: M3; Solar_Connector
J6, J7, J8, J9: Bolt; Nut_Bolt
U1: Motor_Driver1; H_Bridge
U2: Motor_Driver2; H_Bridge
U3: Motor_Driver3; H_Bridge

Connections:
+12V: F2.1, F3.1, J2.1
/12V: F1.1, J10.1
/EN1: J4.1, U1.3
/EN2: J4.4, U2.3
/EN3: J4.8, U3.3
/G: J10.2, U1.7
/I1A: J4.6, U1.4
/I1B: J4.7, U1.5
/I2A: J4.3, U2.4
/I2B: J4.2, U2.5
/I3A: J4.9, U3.4
/I3B: J4.5, U3.5
GND: J2.2, U2.7, U3.7
unnamed: F1.2, U1.6
unnamed: F2.2, U2.6
unnamed: F3.2, U3.6
unnamed: J1.1, U1.1
unnamed: J1.2, U1.2
unnamed: J3.1, U2.1
unnamed: J3.2, U2.2
unnamed: J5.1, U3.1
unnamed: J5.2, U3.2
